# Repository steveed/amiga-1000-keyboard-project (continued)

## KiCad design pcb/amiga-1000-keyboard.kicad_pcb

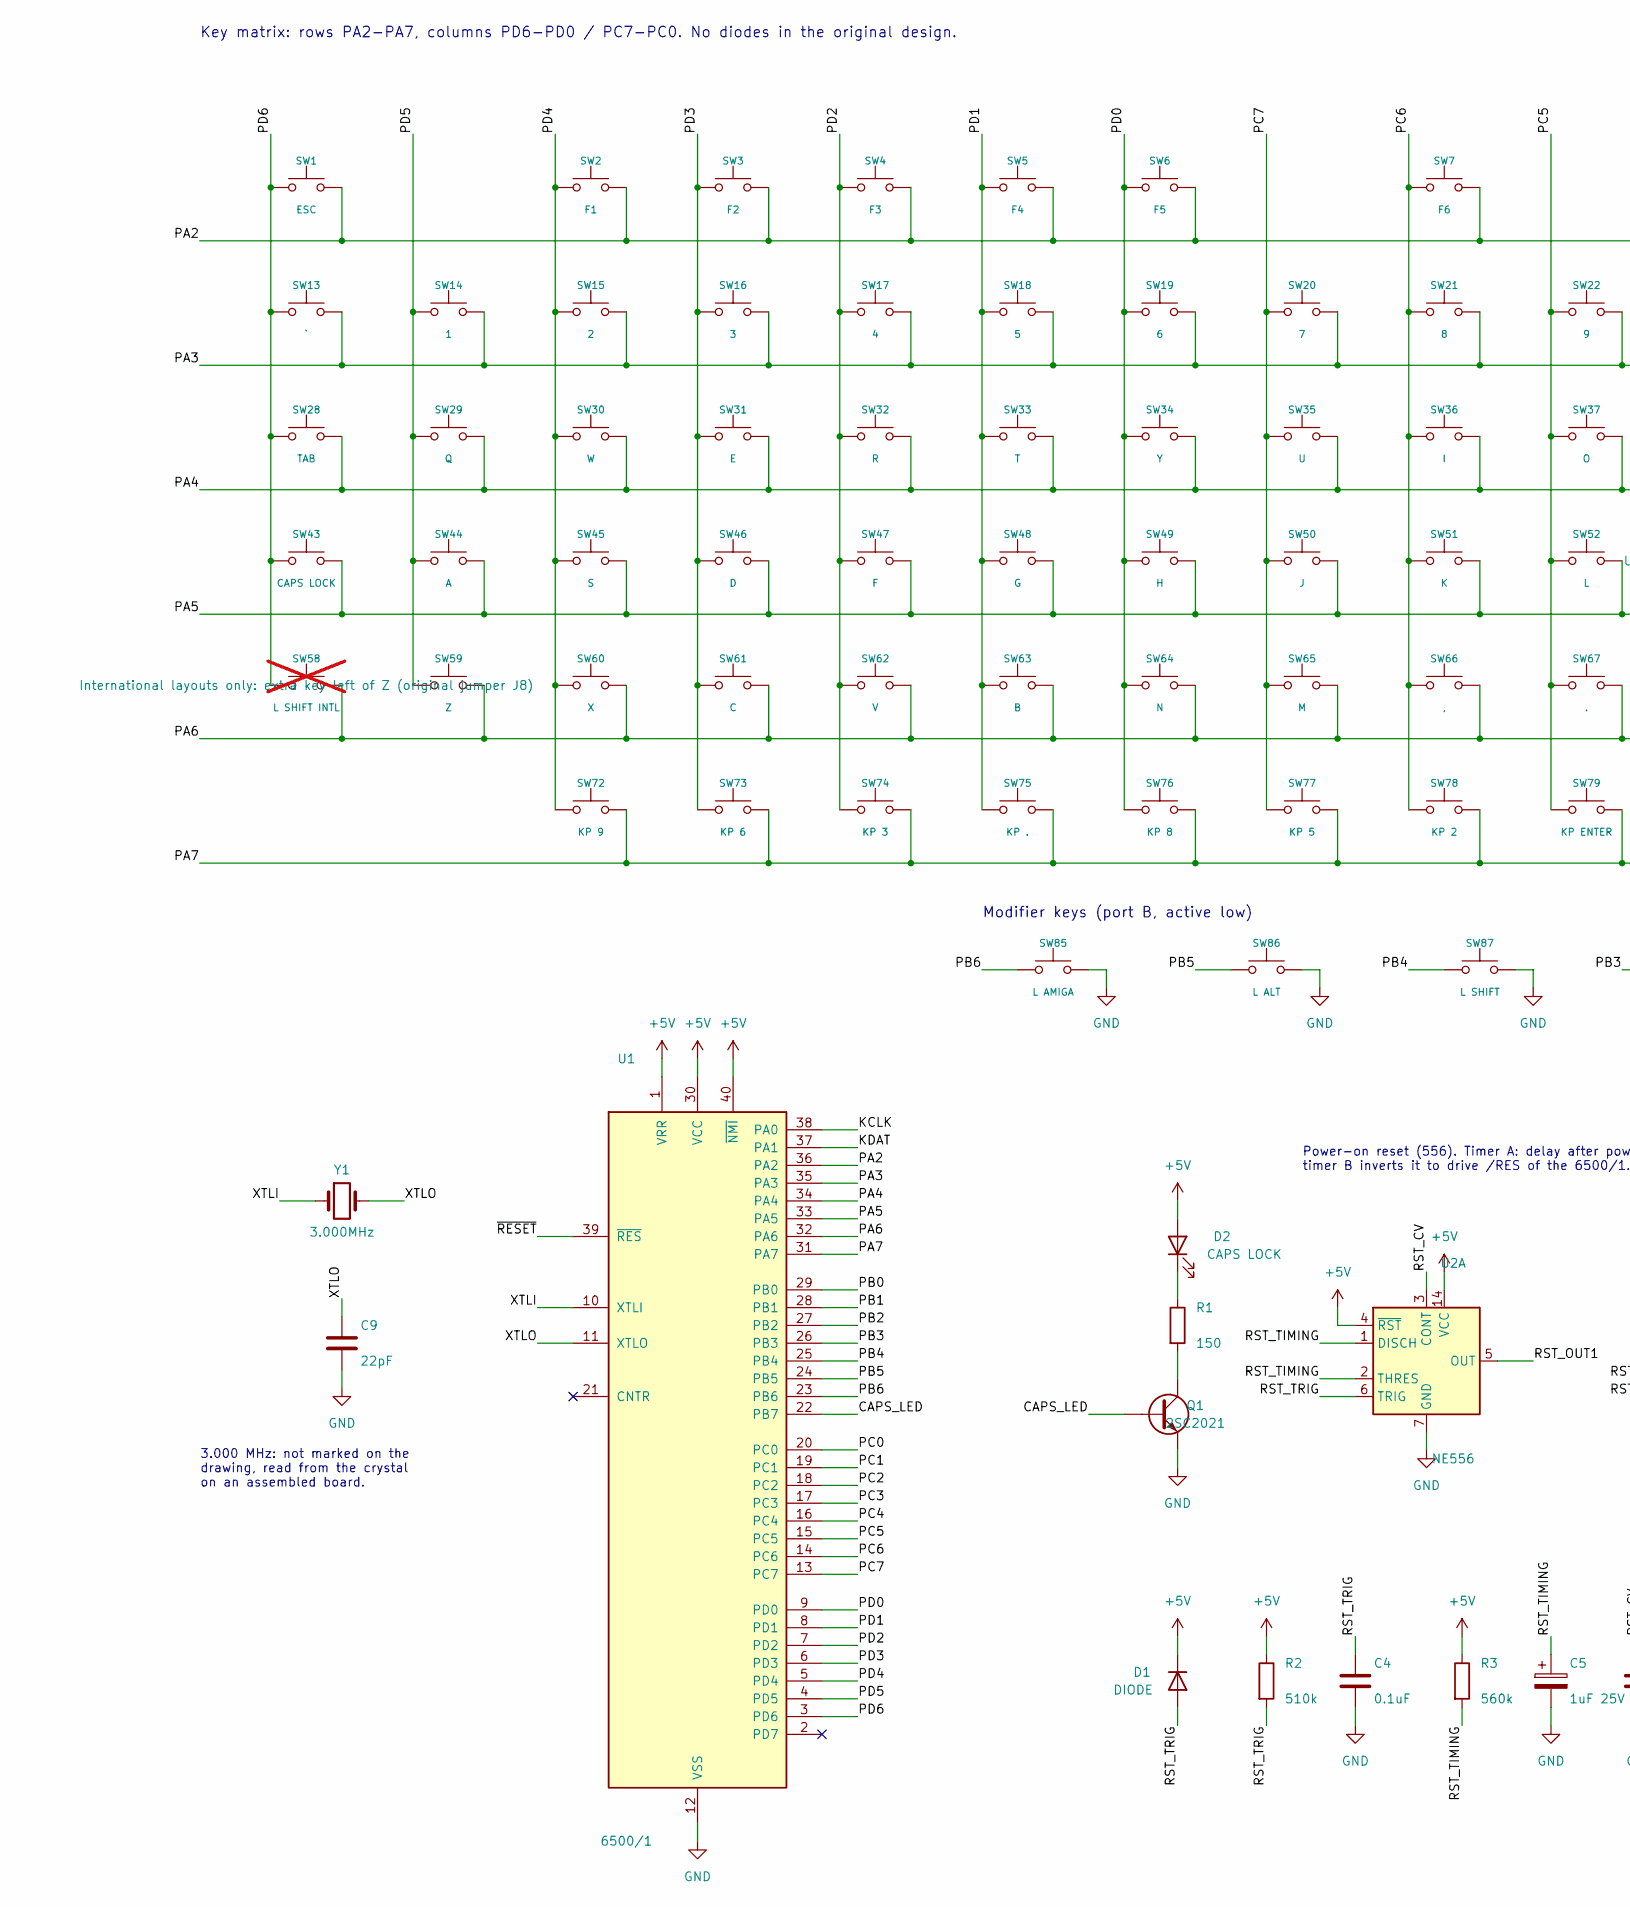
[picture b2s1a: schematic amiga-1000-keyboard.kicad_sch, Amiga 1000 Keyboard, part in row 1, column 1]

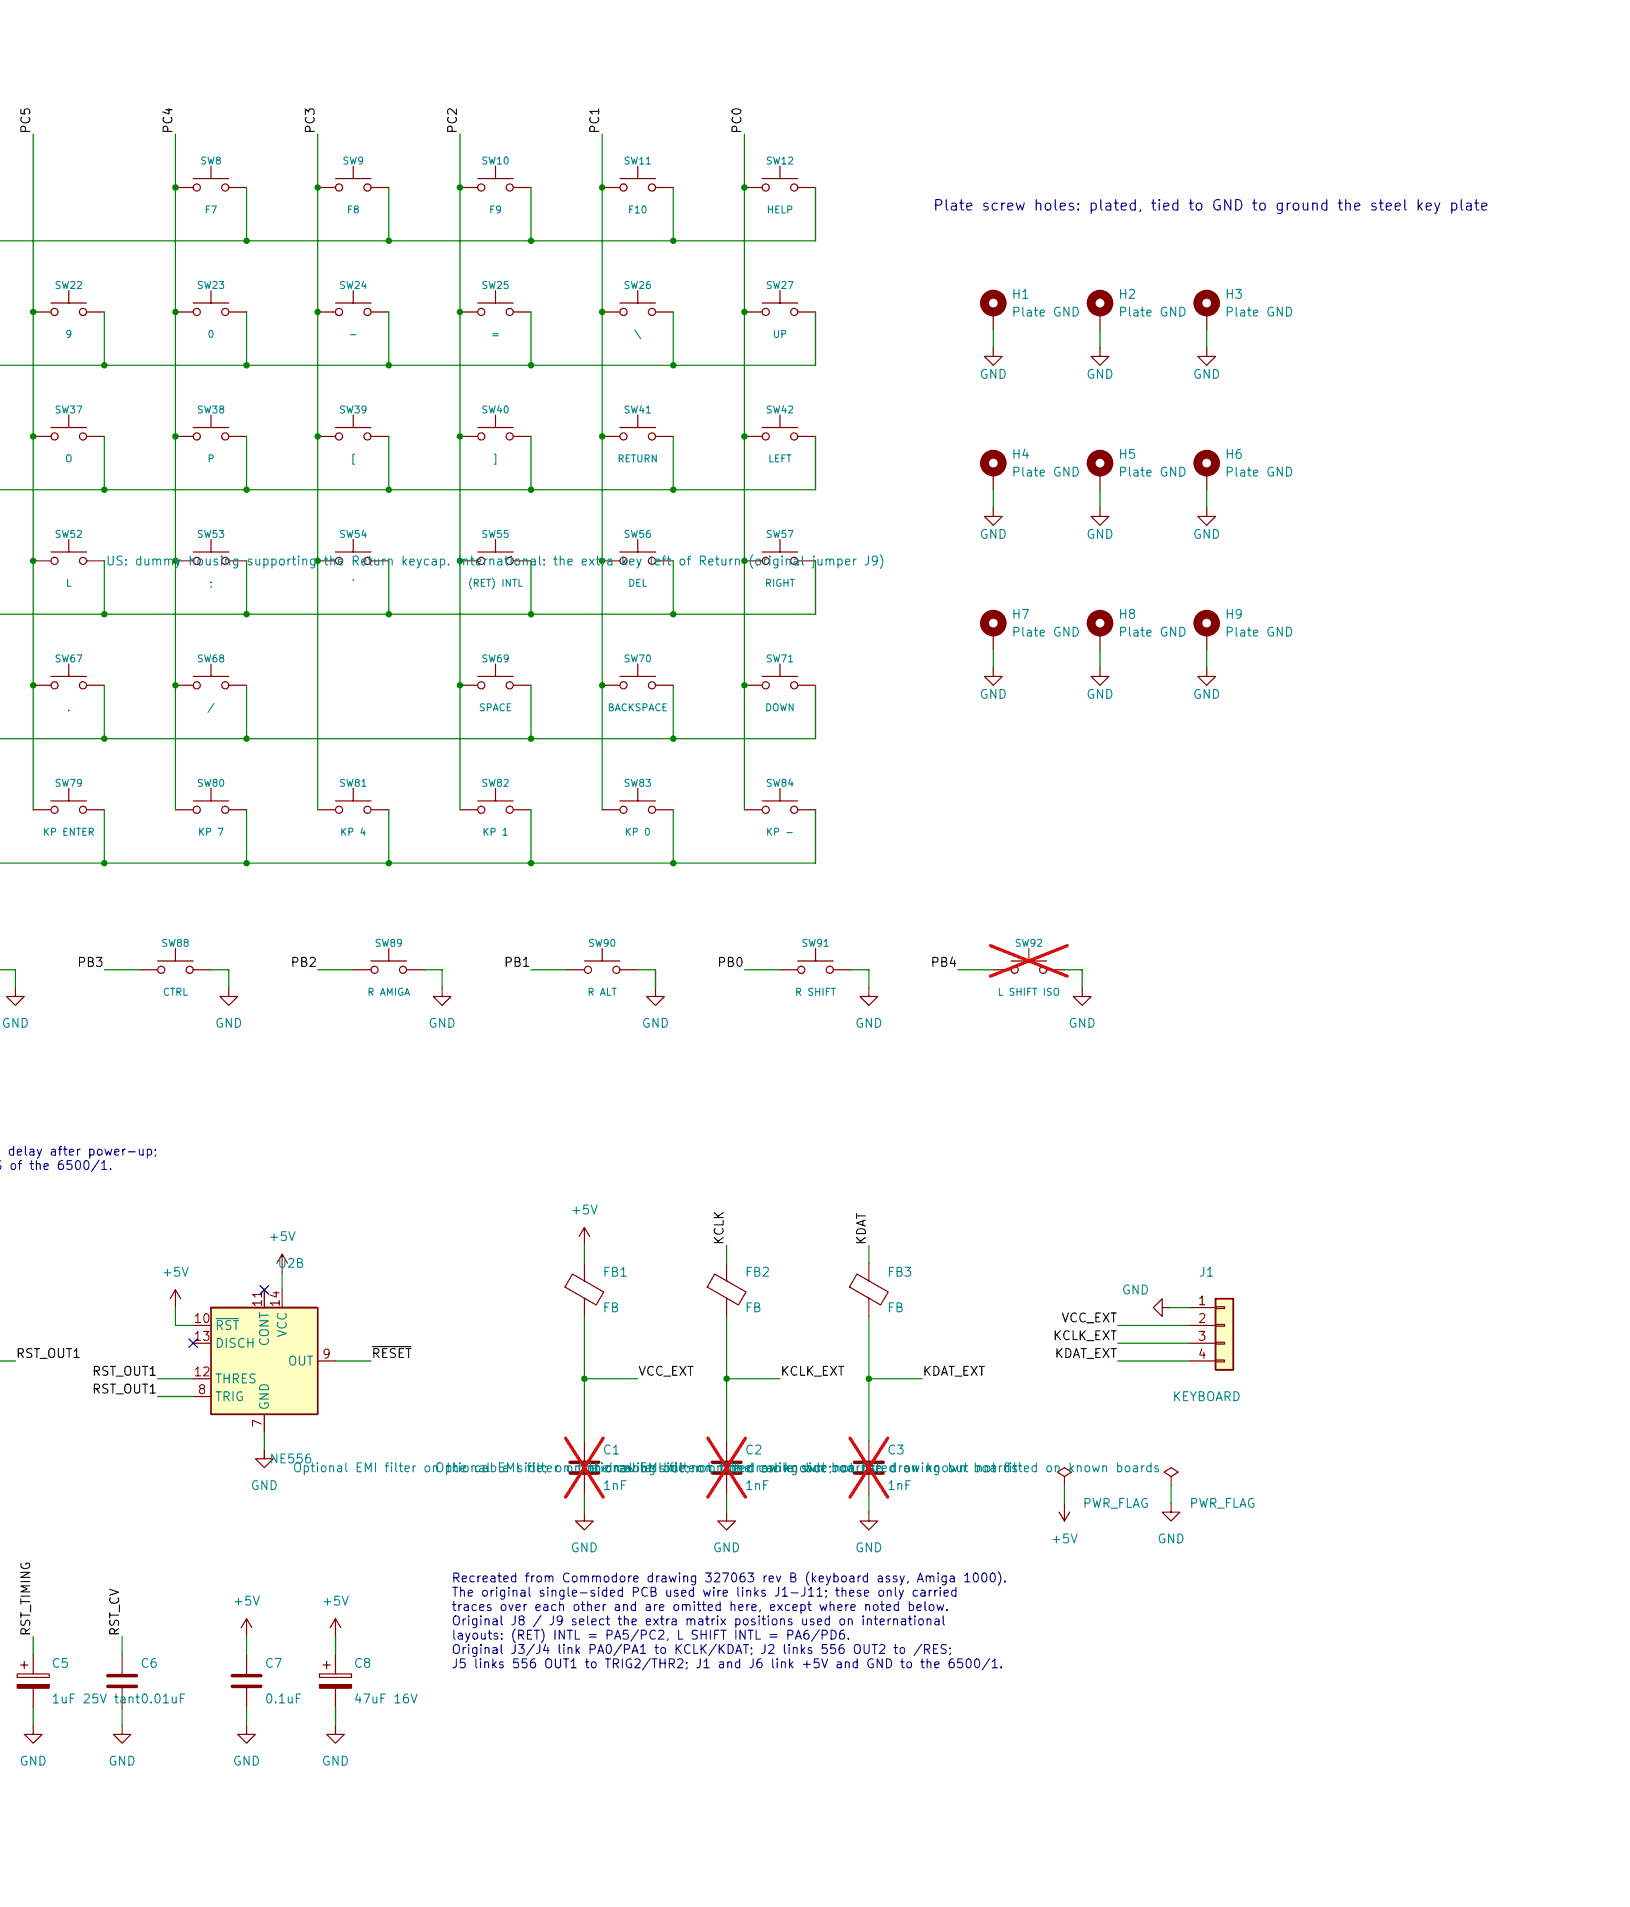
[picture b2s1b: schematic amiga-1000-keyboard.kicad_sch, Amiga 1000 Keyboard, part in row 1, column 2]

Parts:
C1, C2, C3: 1nF; C_Disc_D5.0mm_W2.5mm_P5.00mm; Part 1nF 50V ceramic disc, 5 mm; not fitted
C4, C7: 0.1uF; C_Disc_D5.0mm_W2.5mm_P5.00mm; Part 100nF 50V ceramic disc, 5 mm
C5: 1uF 25V tant; CP_Radial_Tantal_D4.5mm_P2.50mm; Part 1uF 25V tantalum, 2.5 mm
C6: 0.01uF; C_Disc_D5.0mm_W2.5mm_P5.00mm; Part 10nF 50V ceramic disc, 5 mm
C8: 47uF 16V; CP_Radial_D5.0mm_P2.00mm; Part 47uF 16V electrolytic, 5 mm dia, 2 mm
C9: 22pF; C_Disc_D5.0mm_W2.5mm_P5.00mm; Part 22pF 50V C0G ceramic disc, 5 mm
D1: DIODE; D_DO-35_SOD27_P7.62mm_Horizontal; Part 1N4148 small-signal diode, DO-35 (origi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
D2: CAPS LOCK; Mitsumi_A1000_CapsLock_LED; Part LED built into the Caps Lock switch (no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
FB1, FB2, FB3: FB; L_Axial_L9.5mm_D4.0mm_P12.70mm_Horizontal_Fastron_SMCC; Part Axial ferrite bead, e.g. Fair-Rite 2743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
H1, H2, H3, H4, H5, H6, H7, H8, H9: Plate GND; MountingHole_3.8mm_Plate_GND
J1: KEYBOARD; PinHeader_1x04_P2.54mm_Vertical; Part Original 4-wire cable soldered in (or a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
Q1: 2SC2021; TO-92_Inline_Wide_ECB; Part 2SC2021 (Rohm SPT, original) or 2SC1815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
R1: 150; R_Axial_DIN0207_L6.3mm_D2.5mm_P10.16mm_Horizontal; Part 150R 1/4W axial
R2: 510k; R_Axial_DIN0207_L6.3mm_D2.5mm_P10.16mm_Horizontal; Part 510K 1/4W axial
R3: 560k; R_Axial_DIN0207_L6.3mm_D2.5mm_P10.16mm_Horizontal; Part 560K 1/4W axial
SW1: ESC; Mitsumi_A1000_Switch; Part Mitsumi standard mechanical Type 2 (KCT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
SW2: F1; Mitsumi_A1000_Switch; Part Mitsumi standard mechanical Type 2 (KCT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
SW3: F2; Mitsumi_A1000_Switch; Part Mitsumi standard mechanical Type 2 (KCT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
SW4: F3; Mitsumi_A1000_Switch; Part Mitsumi standard mechanical Type 2 (KCT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
SW5: F4; Mitsumi_A1000_Switch; Part Mitsumi standard mechanical Type 2 (KCT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
SW6: F5; Mitsumi_A1000_Switch; Part Mitsumi standard mechanical Type 2 (KCT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
SW7: F6; Mitsumi_A1000_Switch; Part Mitsumi standard mechanical Type 2 (KCT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
SW8: F7; Mitsumi_A1000_Switch; Part Mitsumi standard mechanical Type 2 (KCT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
SW9: F8; Mitsumi_A1000_Switch; Part Mitsumi standard mechanical Type 2 (KCT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
SW10: F9; Mitsumi_A1000_Switch; Part Mitsumi standard mechanical Type 2 (KCT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
SW11: F10; Mitsumi_A1000_Switch; Part Mitsumi standard mechanical Type 2 (KCT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
SW12: HELP; Mitsumi_A1000_Switch; Part Mitsumi standard mechanical Type 2 (KCT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
SW13: `; Mitsumi_A1000_Switch; Part Mitsumi standard mechanical Type 2 (KCT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
SW14: 1; Mitsumi_A1000_Switch; Part Mitsumi standard mechanical Type 2 (KCT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
SW15: 2; Mitsumi_A1000_Switch; Part Mitsumi standard mechanical Type 2 (KCT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
SW16: 3; Mitsumi_A1000_Switch; Part Mitsumi standard mechanical Type 2 (KCT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
SW17: 4; Mitsumi_A1000_Switch; Part Mitsumi standard mechanical Type 2 (KCT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
SW18: 5; Mitsumi_A1000_Switch; Part Mitsumi standard mechanical Type 2 (KCT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
SW19: 6; Mitsumi_A1000_Switch; Part Mitsumi standard mechanical Type 2 (KCT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
SW20: 7; Mitsumi_A1000_Switch; Part Mitsumi standard mechanical Type 2 (KCT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
SW21: 8; Mitsumi_A1000_Switch; Part Mitsumi standard mechanical Type 2 (KCT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
SW22: 9; Mitsumi_A1000_Switch; Part Mitsumi standard mechanical Type 2 (KCT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
SW23: 0; Mitsumi_A1000_Switch; Part Mitsumi standard mechanical Type 2 (KCT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
SW24: -; Mitsumi_A1000_Switch; Part Mitsumi standard mechanical Type 2 (KCT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
SW25: =; Mitsumi_A1000_Switch; Part Mitsumi standard mechanical Type 2 (KCT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
SW26: \; Mitsumi_A1000_Switch; Part Mitsumi standard mechanical Type 2 (KCT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
SW27: UP; Mitsumi_A1000_Switch; Part Mitsumi standard mechanical Type 2 (KCT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
SW28: TAB; Mitsumi_A1000_Switch; Part Mitsumi standard mechanical Type 2 (KCT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
SW29: Q; Mitsumi_A1000_Switch; Part Mitsumi standard mechanical Type 2 (KCT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
SW30: W; Mitsumi_A1000_Switch; Part Mitsumi standard mechanical Type 2 (KCT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
SW31: E; Mitsumi_A1000_Switch; Part Mitsumi standard mechanical Type 2 (KCT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
SW32: R; Mitsumi_A1000_Switch; Part Mitsumi standard mechanical Type 2 (KCT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
SW33: T; Mitsumi_A1000_Switch; Part Mitsumi standard mechanical Type 2 (KCT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
SW34: Y; Mitsumi_A1000_Switch; Part Mitsumi standard mechanical Type 2 (KCT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
SW35: U; Mitsumi_A1000_Switch; Part Mitsumi standard mechanical Type 2 (KCT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
SW36: I; Mitsumi_A1000_Switch; Part Mitsumi standard mechanical Type 2 (KCT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
SW37: O; Mitsumi_A1000_Switch; Part Mitsumi standard mechanical Type 2 (KCT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
SW38: P; Mitsumi_A1000_Switch; Part Mitsumi standard mechanical Type 2 (KCT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
SW39: [; Mitsumi_A1000_Switch; Part Mitsumi standard mechanical Type 2 (KCT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
SW40: ]; Mitsumi_A1000_Switch; Part Mitsumi standard mechanical Type 2 (KCT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
SW41: RETURN; Mitsumi_A1000_Switch; Part Mitsumi standard mechanical Type 2 (KCT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
SW42: LEFT; Mitsumi_A1000_Switch; Part Mitsumi standard mechanical Type 2 (KCT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
SW43: CAPS LOCK; Mitsumi_A1000_Switch; Part Mitsumi standard mechanical Type 2 (KCT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
SW44: A; Mitsumi_A1000_Switch; Part Mitsumi standard mechanical Type 2 (KCT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
SW45: S; Mitsumi_A1000_Switch; Part Mitsumi standard mechanical Type 2 (KCT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
SW46: D; Mitsumi_A1000_Switch; Part Mitsumi standard mechanical Type 2 (KCT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
SW47: F; Mitsumi_A1000_Switch; Part Mitsumi standard mechanical Type 2 (KCT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
SW48: G; Mitsumi_A1000_Switch; Part Mitsumi standard mechanical Type 2 (KCT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
SW49: H; Mitsumi_A1000_Switch; Part Mitsumi standard mechanical Type 2 (KCT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
SW50: J; Mitsumi_A1000_Switch; Part Mitsumi standard mechanical Type 2 (KCT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
SW51: K; Mitsumi_A1000_Switch; Part Mitsumi standard mechanical Type 2 (KCT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
SW52: L; Mitsumi_A1000_Switch; Part Mitsumi standard mechanical Type 2 (KCT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
SW53: ;; Mitsumi_A1000_Switch; Part Mitsumi standard mechanical Type 2 (KCT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
SW54: '; Mitsumi_A1000_Switch; Part Mitsumi standard mechanical Type 2 (KCT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
SW55: (RET) INTL; Mitsumi_A1000_Switch; Part Dummy Mitsumi housing (one leg, no spri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
SW56: DEL; Mitsumi_A1000_Switch; Part Mitsumi standard mechanical Type 2 (KCT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
SW57: RIGHT; Mitsumi_A1000_Switch; Part Mitsumi standard mechanical Type 2 (KCT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
SW58: L SHIFT INTL; Mitsumi_A1000_Switch; Part Mitsumi standard mechanical Type 2 (KCT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; not fitted
SW59: Z; Mitsumi_A1000_Switch; Part Mitsumi standard mechanical Type 2 (KCT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
SW60: X; Mitsumi_A1000_Switch; Part Mitsumi standard mechanical Type 2 (KCT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
SW61: C; Mitsumi_A1000_Switch; Part Mitsumi standard mechanical Type 2 (KCT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
SW62: V; Mitsumi_A1000_Switch; Part Mitsumi standard mechanical Type 2 (KCT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
SW63: B; Mitsumi_A1000_Switch; Part Mitsumi standard mechanical Type 2 (KCT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
SW64: N; Mitsumi_A1000_Switch; Part Mitsumi standard mechanical Type 2 (KCT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
SW65: M; Mitsumi_A1000_Switch; Part Mitsumi standard mechanical Type 2 (KCT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
SW66: ,; Mitsumi_A1000_Switch; Part Mitsumi standard mechanical Type 2 (KCT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
SW67: .; Mitsumi_A1000_Switch; Part Mitsumi standard mechanical Type 2 (KCT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
SW68: /; Mitsumi_A1000_Switch; Part Mitsumi standard mechanical Type 2 (KCT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
SW69: SPACE; Mitsumi_A1000_Switch; Part Mitsumi standard mechanical Type 2 (KCT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
SW70: BACKSPACE; Mitsumi_A1000_Switch; Part Mitsumi standard mechanical Type 2 (KCT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
SW71: DOWN; Mitsumi_A1000_Switch; Part Mitsumi standard mechanical Type 2 (KCT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
SW72: KP 9; Mitsumi_A1000_Switch; Part Mitsumi standard mechanical Type 2 (KCT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
SW73: KP 6; Mitsumi_A1000_Switch; Part Mitsumi standard mechanical Type 2 (KCT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
SW74: KP 3; Mitsumi_A1000_Switch; Part Mitsumi standard mechanical Type 2 (KCT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
SW75: KP .; Mitsumi_A1000_Switch; Part Mitsumi standard mechanical Type 2 (KCT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
SW76: KP 8; Mitsumi_A1000_Switch; Part Mitsumi standard mechanical Type 2 (KCT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
SW77: KP 5; Mitsumi_A1000_Switch; Part Mitsumi standard mechanical Type 2 (KCT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
SW78: KP 2; Mitsumi_A1000_Switch; Part Mitsumi standard mechanical Type 2 (KCT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
SW79: KP ENTER; Mitsumi_A1000_Switch; Part Mitsumi standard mechanical Type 2 (KCT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
SW80: KP 7; Mitsumi_A1000_Switch; Part Mitsumi standard mechanical Type 2 (KCT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
SW81: KP 4; Mitsumi_A1000_Switch; Part Mitsumi standard mechanical Type 2 (KCT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
SW82: KP 1; Mitsumi_A1000_Switch; Part Mitsumi standard mechanical Type 2 (KCT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
SW83: KP 0; Mitsumi_A1000_Switch; Part Mitsumi standard mechanical Type 2 (KCT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
SW84: KP -; Mitsumi_A1000_Switch; Part Mitsumi standard mechanical Type 2 (KCT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
SW85: L AMIGA; Mitsumi_A1000_Switch; Part Mitsumi standard mechanical Type 2 (KCT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
SW86: L ALT; Mitsumi_A1000_Switch; Part Mitsumi standard mechanical Type 2 (KCT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
SW87: L SHIFT; Mitsumi_A1000_Switch; Part Mitsumi standard mechanical Type 2 (KCT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
SW88: CTRL; Mitsumi_A1000_Switch; Part Mitsumi standard mechanical Type 2 (KCT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
SW89: R AMIGA; Mitsumi_A1000_Switch; Part Mitsumi standard mechanical Type 2 (KCT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
SW90: R ALT; Mitsumi_A1000_Switch; Part Mitsumi standard mechanical Type 2 (KCT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
SW91: R SHIFT; Mitsumi_A1000_Switch; Part Mitsumi standard mechanical Type 2 (KCT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
SW92: L SHIFT ISO; Mitsumi_A1000_Switch; Part Mitsumi standard mechanical Type 2 (KCT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; not fitted
U1: 6500/1; DIP-40_W15.24mm; Part Commodore 6500/1 keyboard controller, s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
U2: NE556; DIP-14_W7.62mm; Part NE556N dual timer, DIP-14
Y1: 3.000MHz; Crystal_HC49-U_Horizontal; Part 3.000 MHz crystal, HC-49/U

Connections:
+5V: C7.1, C8.1, D1.1 (K), D2.2 (A), FB1.1, R2.1, R3.1, U1.1 (VRR), U1.30 (VCC), U1.40 (~NMI), U2.4 (~RST), U2.10 (~RST), U2.14 (VCC)
/CAPS_LED: Q1.B, U1.22 (PB7)
/KCLK: FB2.1, U1.38 (PA0)
/KCLK_EXT: C2.1, FB2.2, J1.3
/KDAT: FB3.1, U1.37 (PA1)
/KDAT_EXT: C3.1, FB3.2, J1.4
/PA2: SW1.2, SW2.2, SW3.2, SW4.2, SW5.2, SW6.2, SW7.2, SW8.2, SW9.2, SW10.2, SW11.2, SW12.2, U1.36 (PA2)
/PA3: SW13.2, SW14.2, SW15.2, SW16.2, SW17.2, SW18.2, SW19.2, SW20.2, SW21.2, SW22.2, SW23.2, SW24.2, SW25.2, SW26.2, SW27.2, U1.35 (PA3)
/PA4: SW28.2, SW29.2, SW30.2, SW31.2, SW32.2, SW33.2, SW34.2, SW35.2, SW36.2, SW37.2, SW38.2, SW39.2, SW40.2, SW41.2, SW42.2, U1.34 (PA4)
/PA5: SW43.2, SW44.2, SW45.2, SW46.2, SW47.2, SW48.2, SW49.2, SW50.2, SW51.2, SW52.2, SW53.2, SW54.2, SW55.2, SW56.2, SW57.2, U1.33 (PA5)
/PA6: SW58.2, SW59.2, SW60.2, SW61.2, SW62.2, SW63.2, SW64.2, SW65.2, SW66.2, SW67.2, SW68.2, SW69.2, SW70.2, SW71.2, U1.32 (PA6)
/PA7: SW72.2, SW73.2, SW74.2, SW75.2, SW76.2, SW77.2, SW78.2, SW79.2, SW80.2, SW81.2, SW82.2, SW83.2, SW84.2, U1.31 (PA7)
/PB0: SW91.1, U1.29 (PB0)
/PB1: SW90.1, U1.28 (PB1)
/PB2: SW89.1, U1.27 (PB2)
/PB3: SW88.1, U1.26 (PB3)
/PB4: SW87.1, SW92.1, U1.25 (PB4)
/PB5: SW86.1, U1.24 (PB5)
/PB6: SW85.1, U1.23 (PB6)
/PC0: SW12.1, SW27.1, SW42.1, SW57.1, SW71.1, SW84.1, U1.20 (PC0)
/PC1: SW11.1, SW26.1, SW41.1, SW56.1, SW70.1, SW83.1, U1.19 (PC1)
/PC2: SW10.1, SW25.1, SW40.1, SW55.1, SW69.1, SW82.1, U1.18 (PC2)
/PC3: SW9.1, SW24.1, SW39.1, SW54.1, SW81.1, U1.17 (PC3)
/PC4: SW8.1, SW23.1, SW38.1, SW53.1, SW68.1, SW80.1, U1.16 (PC4)
/PC5: SW22.1, SW37.1, SW52.1, SW67.1, SW79.1, U1.15 (PC5)
/PC6: SW7.1, SW21.1, SW36.1, SW51.1, SW66.1, SW78.1, U1.14 (PC6)
/PC7: SW20.1, SW35.1, SW50.1, SW65.1, SW77.1, U1.13 (PC7)
/PD0: SW6.1, SW19.1, SW34.1, SW49.1, SW64.1, SW76.1, U1.9 (PD0)
/PD1: SW5.1, SW18.1, SW33.1, SW48.1, SW63.1, SW75.1, U1.8 (PD1)
/PD2: SW4.1, SW17.1, SW32.1, SW47.1, SW62.1, SW74.1, U1.7 (PD2)
/PD3: SW3.1, SW16.1, SW31.1, SW46.1, SW61.1, SW73.1, U1.6 (PD3)
/PD4: SW2.1, SW15.1, SW30.1, SW45.1, SW60.1, SW72.1, U1.5 (PD4)
/PD5: SW14.1, SW29.1, SW44.1, SW59.1, U1.4 (PD5)
/PD6: SW1.1, SW13.1, SW28.1, SW43.1, SW58.1, U1.3 (PD6)
/RST_CV: C6.1, U2.3 (CONT)
/RST_OUT1: U2.5 (OUT), U2.8 (TRIG), U2.12 (THRES)
/RST_TIMING: C5.1, R3.2, U2.1 (DISCH), U2.2 (THRES)
/RST_TRIG: C4.1, D1.2 (A), R2.2, U2.6 (TRIG)
/VCC_EXT: C1.1, FB1.2, J1.2
/XTLI: U1.10 (XTLI), Y1.1
/XTLO: C9.1, U1.11 (XTLO), Y1.2
/~RESET: U1.39 (~RES), U2.9 (OUT)
GND: C1.2, C2.2, C3.2, C4.2, C5.2, C6.2, C7.2, C8.2, C9.2, H1.1, H2.1, H3.1, H4.1, H5.1, H6.1, H7.1, H8.1, H9.1, J1.1, Q1.E, SW85.2, SW86.2, SW87.2, SW88.2, SW89.2, SW90.2, SW91.2, SW92.2, U1.12 (VSS), U2.7 (GND)
unnamed: D2.1 (K), R1.1
unnamed: Q1.C, R1.2

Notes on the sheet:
Key matrix: rows PA2-PA7, columns PD6-PD0 / PC7-PC0. No diodes in the original design.
Recreated from Commodore drawing 327063 rev B (keyboard assy, Amiga 1000). The original single-sided PCB used wire links J1-J11; these only carried traces over each other and are omitted here, except where noted below. Original J8 / J9 select the extra matrix positions used on international layouts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
Modifier keys (port B, active low)
3.000 MHz: not marked on the drawing, read from the crystal on an assembled board.
Power-on reset (556). Timer A: delay after power-up; timer B inverts it to drive /RES of the 6500/1.
Plate screw holes: plated, tied to GND to ground the steel key plate

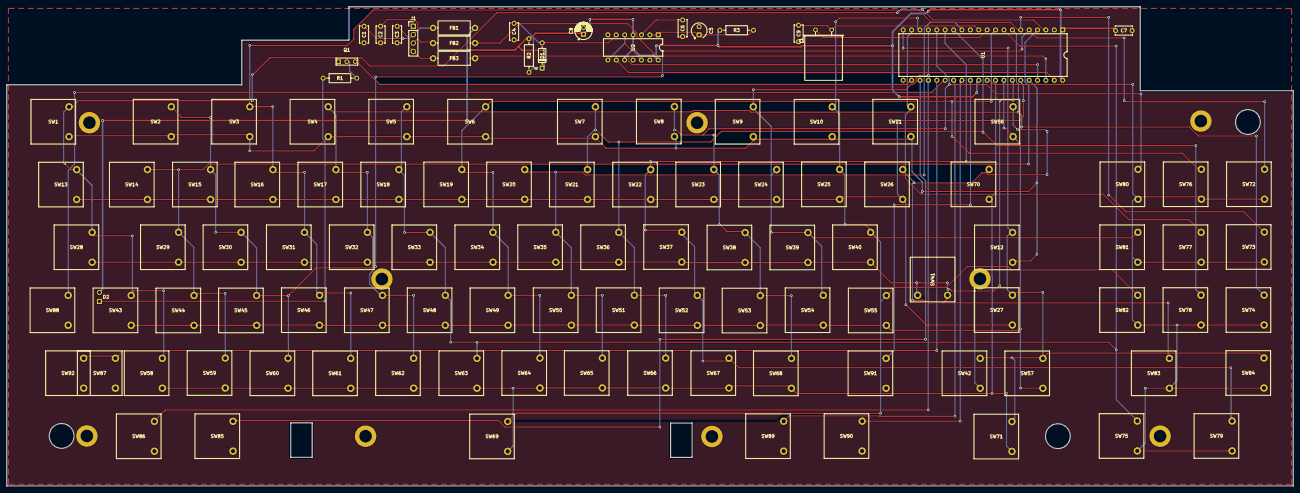
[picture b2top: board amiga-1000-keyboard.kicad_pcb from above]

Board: 2 copper layers, 389.2 x 145.0 mm, 126 parts (0 on the bottom side), 45 nets.

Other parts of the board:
H10, H11, H12: Case 7.5mm; MountingHole_7.5mm_CaseClearance

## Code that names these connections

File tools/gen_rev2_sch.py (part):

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
# ------------------------------------------------------------------ pin map

ROWS = ['PF0', 'PF1', 'PF4', 'PF5', 'PF6', 'PF7', 'PC6', 'PD7']       # driven low one at a time
COLS = ['PB0', 'PB1', 'PB2', 'PB3', 'PB4', 'PB5', 'PB6',              # inputs with pull-ups
        'PD0', 'PD1', 'PD4', 'PD5', 'PD6']
MCU_NETS = {
    'PD2': 'KCLK',            # INT2 / RXD1: Henryk's debug UART also lives on clock and data
    'PD3': 'KDAT',            # INT3 / TXD1
    'PB7': 'CAPS_LED',        # OC1C, can dim the LED
    'PE6': 'AMIGA_PWR',       # TPS2116 ST: high while the Amiga's 5 V is the supply in use
    '~{HWB}/PE2': 'HWB',      # held low at reset -> USB bootloader
    'PC7': 'SPARE',           # brought out to a test pad
    '~{RESET}': 'RESET',
    'XTAL1': 'XTAL1', 'XTAL2': 'XTAL2',
    'D+': 'USB_DP_MCU', 'D-': 'USB_DN_MCU',
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    place('Connector_Generic:Conn_02x03_Odd_Even', 'J3', 'ISP', 180.34, 200.66,
          {'1': 'COL3', '2': '+5V', '3': 'COL1', '4': 'COL2', '5': 'RESET', '6': 'GND'},
          'Connector_PinHeader_2.54mm:PinHeader_2x03_P2.54mm_Vertical', 'AVR ISP header (recovery only)',
          dnp=True, desc='MISO/PB3, SCK/PB1 and MOSI/PB2 are shared with matrix columns 3, 1 and 2')
    place('Connector:TestPoint', 'TP1', 'SPARE (PC7)', 233.68, 200.66, {'1': 'SPARE'},
          'TestPoint:TestPoint_Pad_D1.5mm', 'test pad', in_bom=False)
    # Caps Lock LED, a 3 mm LED through the Caps Lock switch
    R('R3', '330', 175.26, 233.68, 'CAPS_LED', 'CAPS_LED_A')
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        wire(sx, sy, ax, sy)
        wire(ax, sy, ax, ay)
        if ref == 'SW87':
            label('SW87_A', ax, sy, (0, -1))
    # SW92 beside the grid, on SW87's anode node
    sw = place('Switch:SW_Push', 'SW92', names['SW92'], x0 + 12 * dx, y0 + 4 * dy,
               {'1': f'COL{cells["SW87"][1]}', '2': 'SW87_A'}, switch_fp(names['SW92']),
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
